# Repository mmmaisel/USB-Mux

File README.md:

# USB-Mux

USB-Mux is an Open-Source and Open-Hardware 2x2 USB 2.0 multiplexer.

It supports a single connection between one of the inputs to one of the outputs.
Additionally, it can disconnect the outputs completely. Power flows from the
selected input to the selected output. Inactive output ports are powerless.

Possible applications are switching USB connections in automated tests
or power-cycle a hanging USB device via software.

Binary production files can be downloaded from the
[Releases](https://github.com/mmmaisel/USB-Mux/releases) page.

## Usage

The multiplexer is controlled over USB via a virtual terminal. The virtual
terminal will prompt "Mux:" and accepts a single number between 0 and 4 followed
by a newline to select the multiplexer position.
The meaning of the different numbers is printed on the PCB.

To connect to the virtual terminal on Linux you can use the following command:
`picocom /dev/ttyACM0`

## Programming

Configure the firmware build environment in the 'src' directory with meson
and the supplied cross compiler file.
`meson . build --cross-file cross.build`
Then go into the 'build' directory and build it with `ninja`.

Now, you can program the CPU on the USB-Mux PCB with OpenOCD and an ST-Nucleo
board as programmer with `ninja flash`.

## License

USB-Mux KiCAD hardware design files in the "hw" directory are licenses under the
CERN-OHL-S v2, or (at your option) any later version.

The USB-Mux firmware in the "src" directory is licensed under the
GNU GPLv3, or (at your option) any later version.

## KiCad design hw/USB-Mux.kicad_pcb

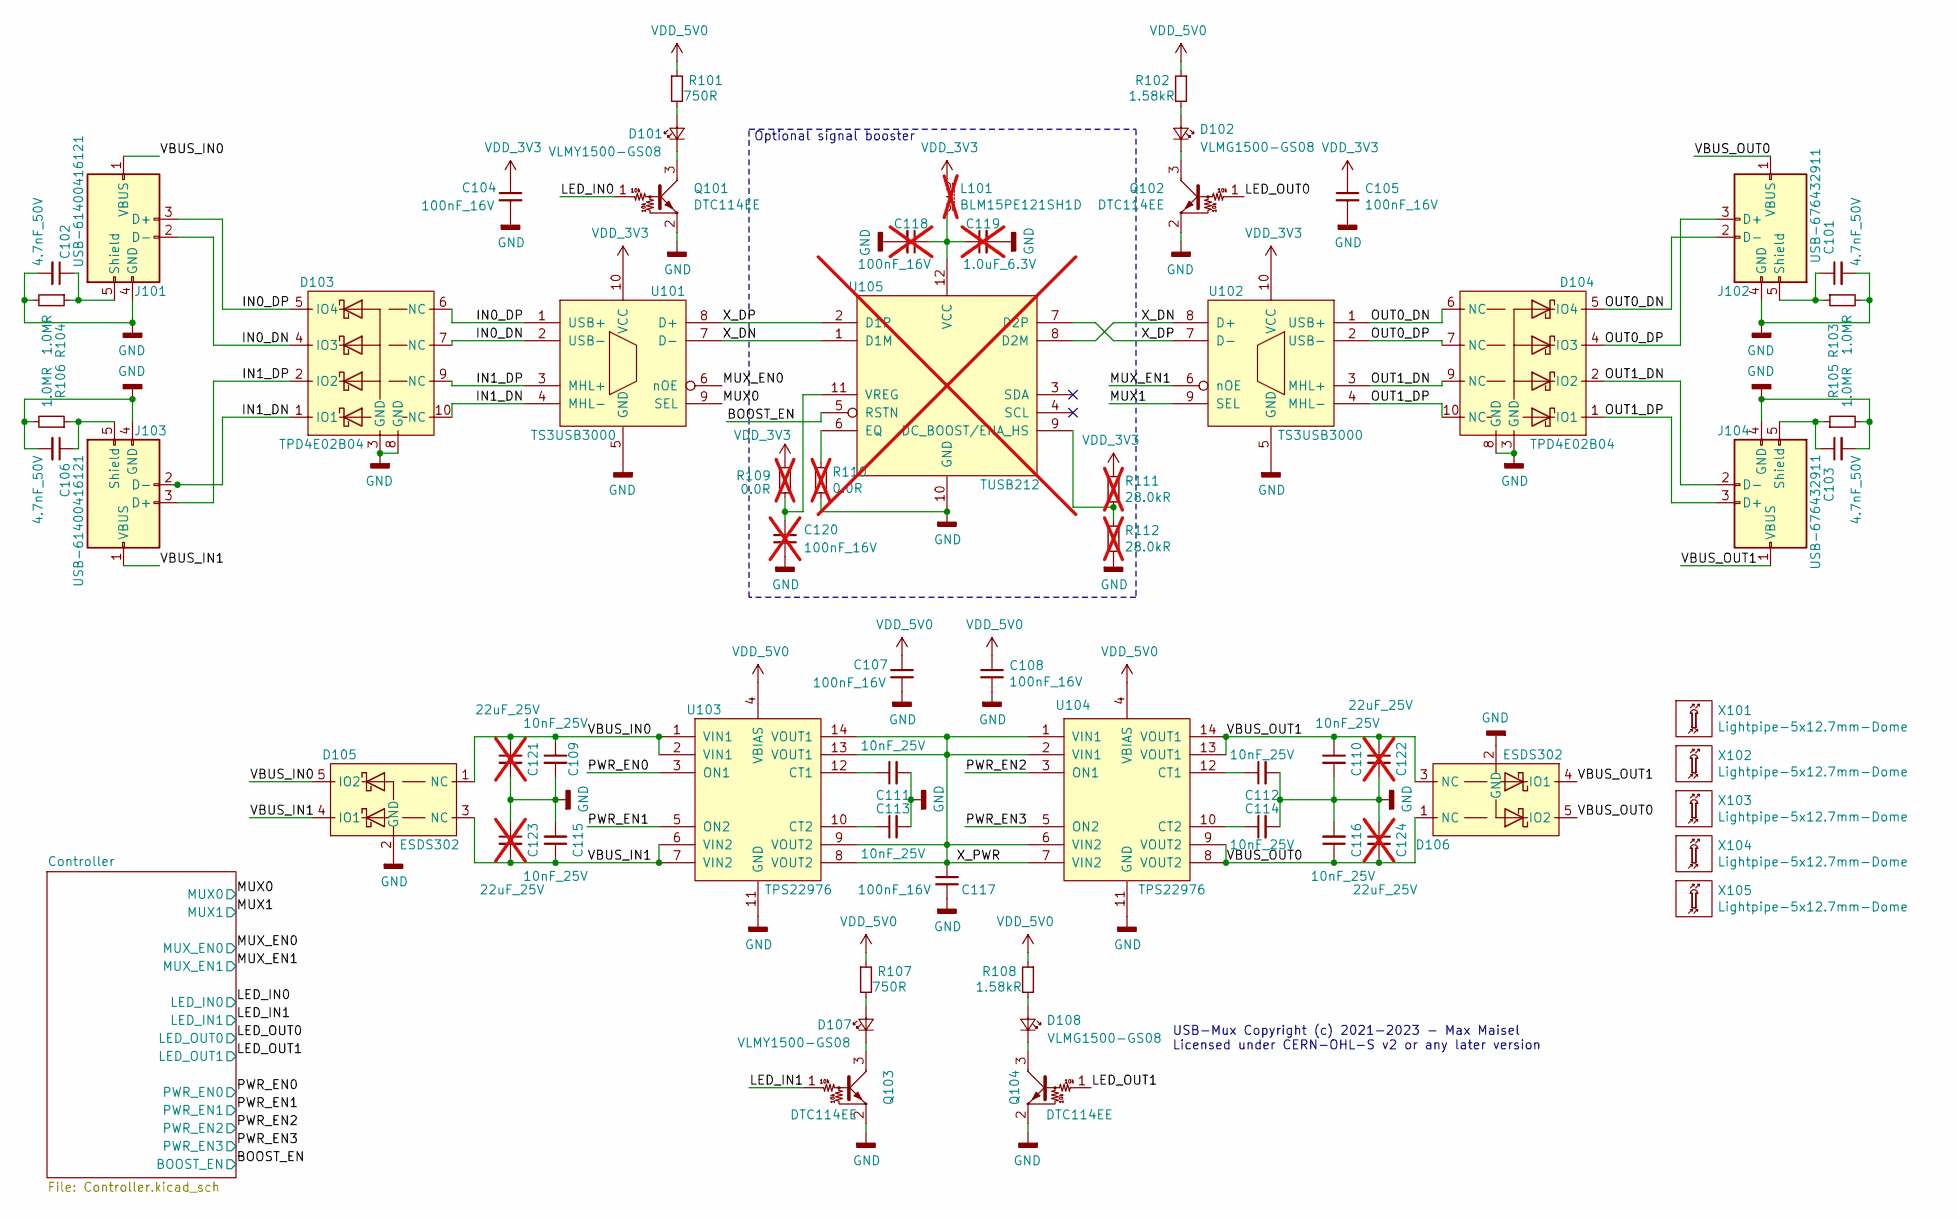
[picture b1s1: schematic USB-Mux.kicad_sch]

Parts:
C101, C102, C103, C106: 4.7nF_50V; C_0402; mouser# 810-CGA2B2X7R1H472K
C104, C105, C107, C108, C117: 100nF_16V; C_0402; mouser# 80-C0402C104K4R
C109, C110, C111, C112, C113, C114, C115, C116: 10nF_25V; C_0402; mouser# 603-CC0402KRX5R8BB10
C118, C120: 100nF_16V; C_0402; mouser# 80-C0402C104K4R; not fitted
C119: 1.0uF_6.3V; C_0402; mouser# 81-GRM152R60J105ME5D; not fitted
C121, C122, C123, C124: 22uF_25V; C_1206; mouser# 81-GRT31CR61E226ME1L; not fitted
D101, D107: VLMY1500-GS08; LED_0402; mouser# 78-VLMY1500-GS08
D102, D108: VLMG1500-GS08; LED_0402; mouser# 78-VLMG1500-GS08
D103, D104: TPD4E02B04; USON10; mouser# 595-TPD4E02B04DQAR
D105, D106: ESDS302; SOT-23-5; mouser# 595-ESDS302DBVR
J101, J103: USB-61400416121
J102, J104: USB-676432911; mouser# 649-87520-0012BLF
L101: BLM15PE121SH1D; L_0402; mouser# 81-BLM15PE121SH1D; not fitted
Q101, Q102, Q103, Q104: DTC114EE; SC-75; mouser# 863-DTC114EET1G
R101, R107: 750R; R_0402; mouser# 667-ERJ-XGNF7500Y
R102, R108: 1.58kR; R_0402; mouser# 667-ERJ-2RKF1581X
R103, R104, R105, R106: 1.0MR; R_0402; mouser# 667-ERJ-2RKF1004X
R109, R110: 0.0R; R_0402; mouser# 667-ERJ-2GE0R00X; not fitted
R111, R112: 28.0kR; R_0402; mouser# 667-ERJ-2RKF2802X; not fitted
U101, U102: TS3USB3000; UQFN10-RSE; mouser# 595-TS3USB3000RSER
U103, U104: TPS22976; WSON-14
U105: TUSB212; X2QFN12-RWB; mouser# 595-TUSB212RWBR; not fitted
X101, X102, X103, X104, X105: Lightpipe-5x12.7mm-Dome; Lightpipe-51513530500F; mouser# 645-51513530500F

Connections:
/BOOST_EN: U105.5 (RSTN); also elsewhere on the board
/IN0_DN: D103.4 (IO3), D103.7 (NC), J101.2 (D-), U101.2 (USB-)
/IN0_DP: D103.5 (IO4), D103.6 (NC), J101.3 (D+), U101.1 (USB+)
/IN1_DN: D103.1 (IO1), D103.10 (NC), J103.2 (D-), U101.4 (MHL-)
/IN1_DP: D103.2 (IO2), D103.9 (NC), J103.3 (D+), U101.3 (MHL+)
/LED_IN0: Q101.1 (B); also elsewhere on the board
/LED_IN1: Q103.1 (B); also elsewhere on the board
/LED_OUT0: Q102.1 (B); also elsewhere on the board
/LED_OUT1: Q104.1 (B); also elsewhere on the board
/MUX0: U101.9 (SEL); also elsewhere on the board
/MUX1: U102.9 (SEL); also elsewhere on the board
/MUX_EN0: U101.6 (nOE); also elsewhere on the board
/MUX_EN1: U102.6 (nOE); also elsewhere on the board
/OUT0_DN: D104.5 (IO4), D104.6 (NC), J102.2 (D-), U102.1 (USB+)
/OUT0_DP: D104.4 (IO3), D104.7 (NC), J102.3 (D+), U102.2 (USB-)
/OUT1_DN: D104.2 (IO2), D104.9 (NC), J104.2 (D-), U102.3 (MHL+)
/OUT1_DP: D104.1 (IO1), D104.10 (NC), J104.3 (D+), U102.4 (MHL-)
/PWR_EN0: U103.3 (ON1); also elsewhere on the board
/PWR_EN1: U103.5 (ON2); also elsewhere on the board
/PWR_EN2: U104.3 (ON1); also elsewhere on the board
/PWR_EN3: U104.5 (ON2); also elsewhere on the board
/VBUS_IN0: C109.1, C121.1, D105.1 (NC), D105.5 (IO2), J101.1 (VBUS), U103.1 (VIN1), U103.2 (VIN1)
/VBUS_IN1: C115.1, C123.2, D105.3 (NC), D105.4 (IO1), J103.1 (VBUS), U103.6 (VIN2), U103.7 (VIN2)
/VBUS_OUT0: C116.1, C124.2, D106.1 (NC), D106.5 (IO2), J102.1 (VBUS), U104.8 (VOUT2), U104.9 (VOUT2)
/VBUS_OUT1: C110.1, C122.1, D106.3 (NC), D106.4 (IO1), J104.1 (VBUS), U104.13 (VOUT1), U104.14 (VOUT1)
/X_DN: U101.7 (D-), U102.8 (D+), U105.1 (D1M), U105.8 (D2M)
/X_DP: U101.8 (D+), U102.7 (D-), U105.2 (D1P), U105.7 (D2P)
/X_PWR: C117.1, U103.8 (VOUT2), U103.9 (VOUT2), U103.13 (VOUT1), U103.14 (VOUT1), U104.1 (VIN1), U104.2 (VIN1), U104.6 (VIN2), U104.7 (VIN2)
GND: C101.2, C102.2, C103.2, C104.2, C105.2, C106.2, C107.2, C108.2, C109.2, C110.2, C111.2, C112.2, C113.2, C114.2, C115.2, C116.2, C117.2, C118.2, C119.2, C120.2, C121.2, C122.2, C123.1, C124.1, D103.3 (GND), D103.8 (GND), D104.3 (GND), D104.8 (GND), D105.2 (GND), D106.2 (GND), J101.4 (GND), J102.4 (GND), J103.4 (GND), J104.4 (GND), Q101.2 (E), Q102.2 (E), Q103.2 (E), Q104.2 (E), R103.2, R104.2, R105.2, R106.2, R110.2, R112.2, U101.5 (GND), U102.5 (GND), U103.11 (GND), U104.11 (GND), U105.10 (GND); also elsewhere on the board
unnamed: C101.1, J102.5 (Shield), R103.1
unnamed: C102.1, J101.5 (Shield), R104.1
unnamed: C103.1, J104.5 (Shield), R105.1
unnamed: C106.1, J103.5 (Shield), R106.1
unnamed: C111.1, U103.12 (CT1)
unnamed: C112.1, U104.12 (CT1)
unnamed: C113.1, U103.10 (CT2)
unnamed: C114.1, U104.10 (CT2)
unnamed: C118.1, C119.1, L101.2, U105.12 (VCC)
unnamed: C120.1, R109.1, U105.11 (VREG)
unnamed: D101.1 (K), Q101.3 (C)
unnamed: D101.2 (A), R101.2
unnamed: D102.1 (K), Q102.3 (C)
unnamed: D102.2 (A), R102.2
unnamed: D107.1 (K), Q103.3 (C)
unnamed: D107.2 (A), R107.2
unnamed: D108.1 (K), Q104.3 (C)
unnamed: D108.2 (A), R108.2
unnamed: R110.1, U105.6 (EQ)
unnamed: R111.2, R112.1, U105.9 (DC_BOOST/ENA_HS)
VDD_3V3: C104.1, C105.1, L101.1, R109.2, R111.1, U101.10 (VCC), U102.10 (VCC); also elsewhere on the board
VDD_5V0: C107.1, C108.1, R101.1, R102.1, R107.1, R108.1, U103.4 (VBIAS), U104.4 (VBIAS); also elsewhere on the board

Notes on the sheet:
Optional signal booster
USB-Mux Copyright (c) 2021-2023 - Max Maisel Licensed under CERN-OHL-S v2 or any later version

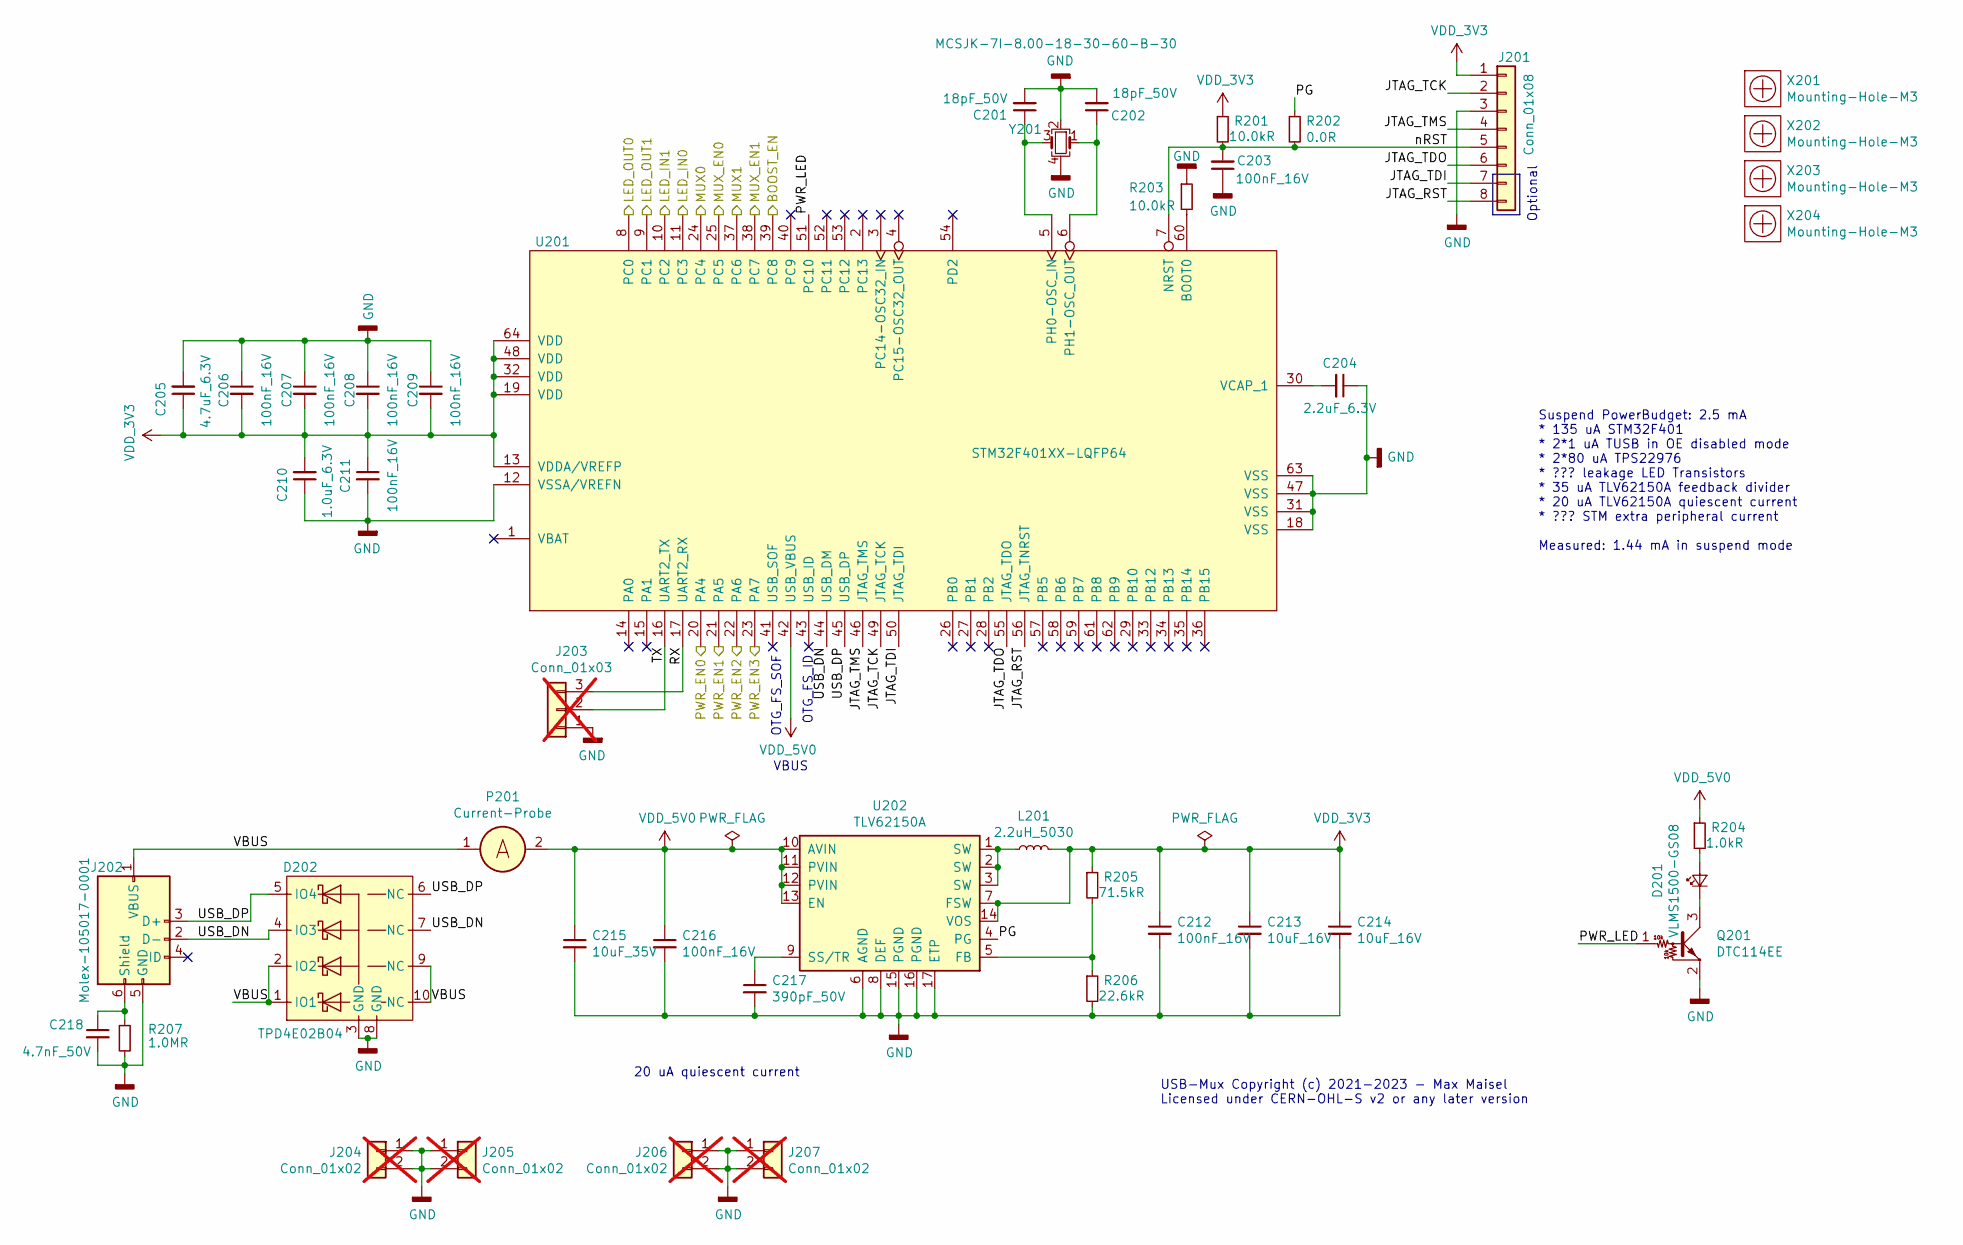
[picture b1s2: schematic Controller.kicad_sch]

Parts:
C201, C202: 18pF_50V; C_0402; mouser# 81-GRM1555C1H180FA1D
C203, C206, C207, C208, C209, C211, C212, C216: 100nF_16V; C_0402; mouser# 80-C0402C104K4R
C204: 2.2uF_6.3V; C_0402; mouser# 81-GRM155R60J225ME9D
C205: 4.7uF_6.3V; C_0402; mouser# 81-GRM155R60J475ME7D
C210: 1.0uF_6.3V; C_0402; mouser# 81-GRM152R60J105ME5D
C213, C214: 10uF_16V; C_1206; mouser# 80-C1206C106K4P
C215: 10uF_35V; C_1210; mouser# 963-GMK325BJ106KN-T
C217: 390pF_50V; C_0402; mouser# 81-GRM155R71H391KA1D
C218: 4.7nF_50V; C_0402; mouser# 810-CGA2B2X7R1H472K
D201: VLMS1500-GS08; LED_0402; mouser# 78-VLMS1500-GS08
D202: TPD4E02B04; USON10; mouser# 595-TPD4E02B04DQAR
J201: Conn_01x08; Pin_Header_Straight_1x08_Pitch2.54mm; farnell# 1593416
J202: Molex-105017-0001; microUSB-B-Molex-1050170-001; mouser# 538-105017-0001
J203: Conn_01x03; Pin_Header_Straight_1x03_Pitch2.54mm; farnell# 1593412; not fitted
J204, J205, J206, J207: Conn_01x02; Pin_Header_Straight_1x02_Pitch2.54mm; farnell# 1593411; not fitted
L201: 2.2uH_5030; L_Taiyo-Yuden_NR-50xx; mouser# 963-NRS5030T2R2NMGJV
P201: Current-Probe; Current-Probe-2.54
Q201: DTC114EE; SC-75; mouser# 863-DTC114EET1G
R201, R203: 10.0kR; R_0402; mouser# 667-ERJ-2RKF1002X
R202: 0.0R; R_0402; mouser# 667-ERJ-2GE0R00X
R204: 1.0kR; R_0402; mouser# 667-ERJ-2RKF1001X
R205: 71.5kR; R_0402; mouser# 667-ERJ-2RKF7152X
R206: 22.6kR; R_0402; mouser# 667-ERJ-S02F2262X
R207: 1.0MR; R_0402; mouser# 667-ERJ-2RKF1004X
U201: STM32F401XX-LQFP64; LQFP-64
U202: TLV62150A; VQFN16-RGT; mouser# 595-TLV62150ARGTR
X201, X202, X203, X204: Mounting-Hole-M3
Y201: MCSJK-7I-8.00-18-30-60-B-30; Crystal_SMD_Multicomp_5032; farnell# 2854013

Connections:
/BOOST_EN: U201.39 (PC8); also elsewhere on the board
/Controller/JTAG_RST: J201.8, U201.56 (JTAG_TNRST)
/Controller/JTAG_TCK: J201.2, U201.49 (JTAG_TCK)
/Controller/JTAG_TDI: J201.7, U201.50 (JTAG_TDI)
/Controller/JTAG_TDO: J201.6, U201.55 (JTAG_TDO)
/Controller/JTAG_TMS: J201.4, U201.46 (JTAG_TMS)
/Controller/PG: R202.1, U202.4 (PG)
/Controller/PWR_LED: Q201.1 (B), U201.51 (PC10)
/Controller/RX: J203.3, U201.17 (UART2_RX)
/Controller/TX: J203.2, U201.16 (UART2_TX)
/Controller/USB_DN: D202.4 (IO3), D202.7 (NC), J202.2 (D-), U201.44 (USB_DM)
/Controller/USB_DP: D202.5 (IO4), D202.6 (NC), J202.3 (D+), U201.45 (USB_DP)
/Controller/VBUS: D202.1 (IO1), D202.2 (IO2), D202.9 (NC), D202.10 (NC), J202.1 (VBUS), P201.1
/Controller/nRST: C203.2, J201.5, R201.2, R202.2, U201.7 (NRST)
/LED_IN0: U201.11 (PC3); also elsewhere on the board
/LED_IN1: U201.10 (PC2); also elsewhere on the board
/LED_OUT0: U201.8 (PC0); also elsewhere on the board
/LED_OUT1: U201.9 (PC1); also elsewhere on the board
/MUX0: U201.24 (PC4); also elsewhere on the board
/MUX1: U201.37 (PC6); also elsewhere on the board
/MUX_EN0: U201.25 (PC5); also elsewhere on the board
/MUX_EN1: U201.38 (PC7); also elsewhere on the board
/PWR_EN0: U201.20 (PA4); also elsewhere on the board
/PWR_EN1: U201.21 (PA5); also elsewhere on the board
/PWR_EN2: U201.22 (PA6); also elsewhere on the board
/PWR_EN3: U201.23 (PA7); also elsewhere on the board
GND: C201.2, C202.2, C203.1, C204.1, C205.2, C206.1, C207.1, C208.1, C209.1, C210.1, C211.2, C212.2, C213.2, C214.2, C215.2, C216.2, C217.2, C218.2, D202.3 (GND), D202.8 (GND), J201.3, J202.5 (GND), J203.1, J204.1, J204.2, J205.1, J205.2, J206.1, J206.2, J207.1, J207.2, Q201.2 (E), R203.1, R206.2, R207.2, U201.12 (VSSA/VREFN), U201.18 (VSS), U201.31 (VSS), U201.47 (VSS), U201.63 (VSS), U202.6 (AGND), U202.8 (DEF), U202.15 (PGND), U202.16 (PGND), U202.17 (ETP), Y201.2, Y201.4; also elsewhere on the board
unnamed: C201.1, U201.5 (PH0-OSC_IN), Y201.3
unnamed: C202.1, U201.6 (PH1-OSC_OUT), Y201.1
unnamed: C204.2, U201.30 (VCAP_1)
unnamed: C217.1, U202.9 (SS/TR)
unnamed: C218.1, J202.6 (Shield), R207.1
unnamed: D201.1 (K), Q201.3 (C)
unnamed: D201.2 (A), R204.2
unnamed: L201.1, U202.1 (SW), U202.2 (SW), U202.3 (SW)
unnamed: R203.2, U201.60 (BOOT0)
unnamed: R205.2, R206.1, U202.5 (FB)
VDD_3V3: C205.1, C206.2, C207.2, C208.2, C209.2, C210.2, C211.1, C212.1, C213.1, C214.1, J201.1, L201.2, R201.1, R205.1, U201.13 (VDDA/VREFP), U201.19 (VDD), U201.32 (VDD), U201.48 (VDD), U201.64 (VDD), U202.7 (FSW), U202.14 (VOS); also elsewhere on the board
VDD_5V0: C215.1, C216.1, P201.2, R204.1, U201.42 (USB_VBUS), U202.10 (AVIN), U202.11 (PVIN), U202.12 (PVIN), U202.13 (EN); also elsewhere on the board

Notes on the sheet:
USB-Mux Copyright (c) 2021-2023 - Max Maisel Licensed under CERN-OHL-S v2 or any later version
VBUS
OTG_FS_SOF
Optional
20 uA quiescent current
OTG_FS_ID
Suspend PowerBudget: 2.5 mA * 135 uA STM32F401 * 2*1 uA TUSB in OE disabled mode * 2*80 uA TPS22976 * ??? leakage LED Transistors * 35 uA TLV62150A feedback divider * 20 uA TLV62150A quiescent current * ??? STM extra peripheral current Measured: 1.44 mA in suspend mode

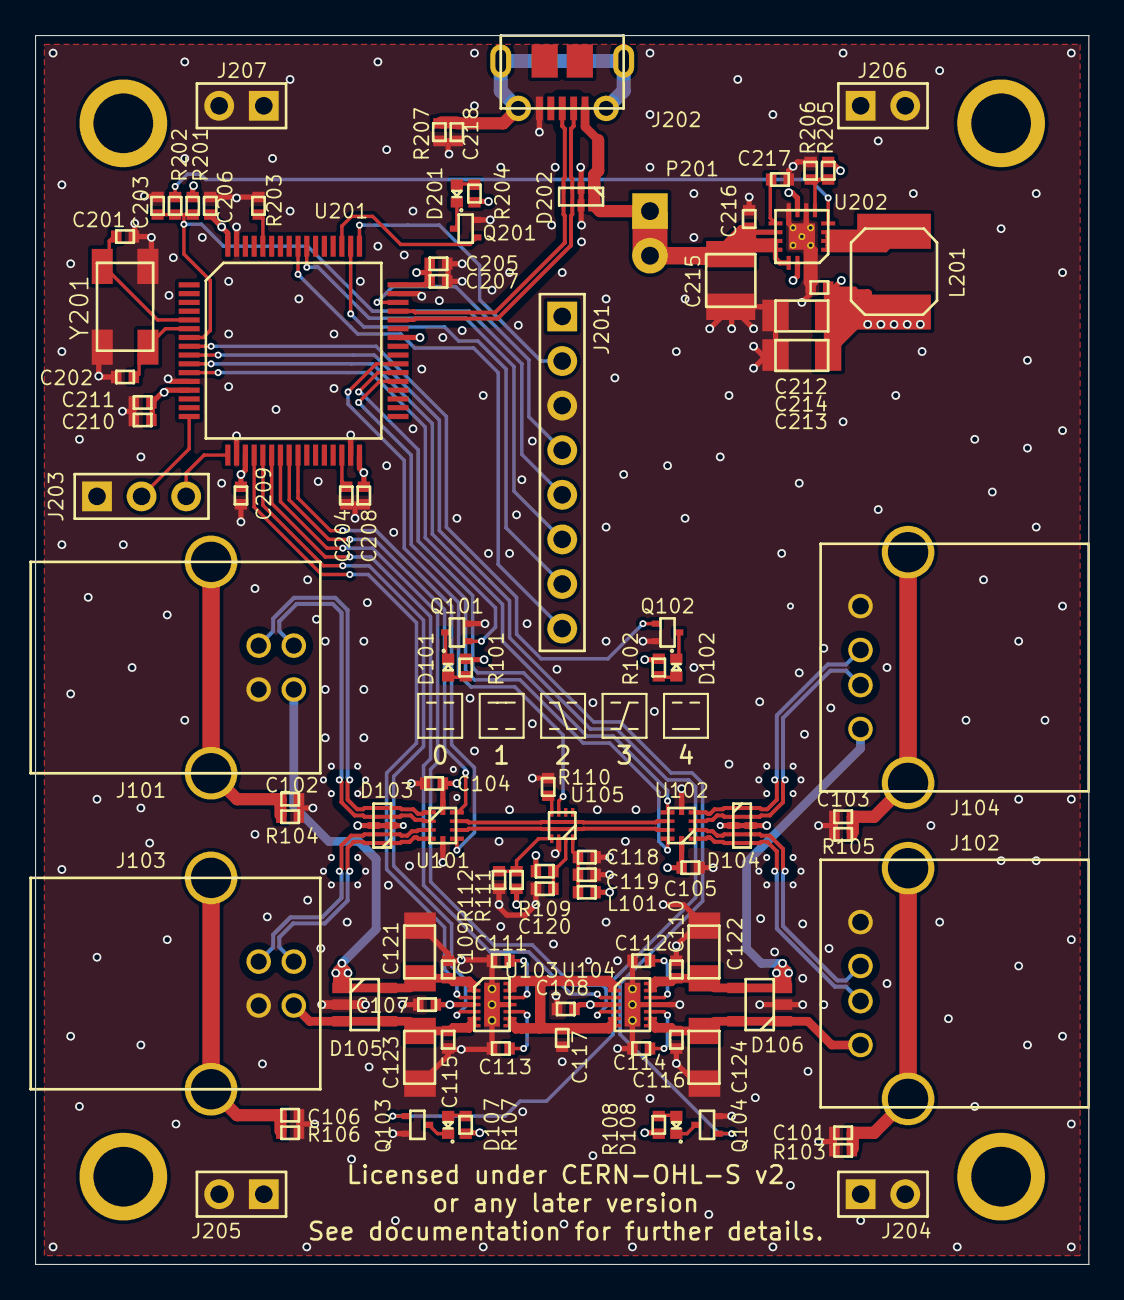
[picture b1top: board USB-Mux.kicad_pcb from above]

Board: 6 copper layers, 60.0 x 70.0 mm, 107 parts (0 on the bottom side), 74 nets.

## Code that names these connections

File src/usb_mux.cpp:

/**********************************************************************\
 * USB-Mux
 *
 * USB-Mux class
 **********************************************************************
 * Copyright (C) 2021 - Max Maisel
 *
 * This program is free software; you can redistribute it and/or
 * modify it under the terms of the GNU General Public License
 * as published by the Free Software Foundation; either version 2
 * of the License, or (at your option) any later version.
 *
 * This program is distributed in the hope that it will be useful,
 * but WITHOUT ANY WARRANTY; without even the implied warranty of
 * MERCHANTABILITY or FITNESS FOR A PARTICULAR PURPOSE.  See the
 * GNU General Public License for more details.
 *
 * You should have received a copy of the GNU General Public License
 * along with this program.  If not, see <http://www.gnu.org/licenses/>.
\**********************************************************************/
#include "usb_mux.h"
#include "pinout.h"
#include "system.h"

#include "dev/gpio.h"
#include "dev/rcc.h"

using namespace dev;
using namespace dev::rcc;
using namespace pinout;

void UsbMux::initialize() {
    RCC->AHB1ENR |= GPIOAEN | GPIOCEN;

    GPIOA->MODER |= MODE_PWREN0 | MODE_PWREN1 | MODE_PWREN2 | MODE_PWREN3;
    GPIOC->PUPDR |= PUPD_MUXDIS0 | PUPD_MUXDIS1 | PUPD_BOOSTDIS;
    GPIOC->MODER |= MODE_LED_OUT0 | MODE_LED_OUT1 |
        MODE_LED_IN0 | MODE_LED_IN1 | MODE_LED_PWR |
        MODE_MUX0 | MODE_MUX1 | MODE_MUXDIS0 | MODE_MUXDIS1 |
        MODE_BOOSTDIS;

    disable_mux();
    GPIOC->set_odr(LED_PWR);
}

void UsbMux::mux(BYTE pos) {
    disable_mux();
    switch(pos) {
        case 1:
            GPIOA->set_odr(PWREN0 | PWREN2);
            sleep_ms(1);
            GPIOC->set_odr(MUX1);
            sleep_ms(1);
            GPIOC->clear_odr(MUXDIS0 | MUXDIS1);
            GPIOC->set_odr(LED_IN0 | LED_OUT0);
            break;
        case 2:
            GPIOA->set_odr(PWREN0 | PWREN3);
            sleep_ms(2);
            GPIOC->clear_odr(MUXDIS0 | MUXDIS1);
            GPIOC->set_odr(LED_IN0 | LED_OUT1);
            break;
        case 3:
            GPIOA->set_odr(PWREN1 | PWREN2);
            sleep_ms(1);
            GPIOC->set_odr(MUX0 | MUX1);
            sleep_ms(1);
            GPIOC->clear_odr(MUXDIS0 | MUXDIS1);
            GPIOC->set_odr(LED_IN1 | LED_OUT0);
            break;
        case 4:
            GPIOA->set_odr(PWREN1 | PWREN3);
            sleep_ms(1);
            GPIOC->set_odr(MUX0);
            sleep_ms(1);
            GPIOC->clear_odr(MUXDIS0 | MUXDIS1);
            GPIOC->set_odr(LED_IN1 | LED_OUT1);
            break;
        default:
            break;
    };
}

void UsbMux::disable_mux() {
    GPIOC->set_odr(MUXDIS0 | MUXDIS1);
    sleep_ms(1);
    GPIOA->clear_odr(
        PWREN0 | PWREN1 | PWREN2 | PWREN3
    );
    GPIOC->clear_odr(
        LED_OUT0 | LED_OUT1 | LED_IN0 | LED_IN1 | MUX0 | MUX1
    );
}

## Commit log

2021-08-02 Add license and readme.
2021-12-30 Commit USB-Mux KiCAD library.
2021-12-30 Add USB-Mux hardware design.
2021-12-30 Fix swapped pin label in USB-Mux schematic.
2021-12-30 Add minimal firmware.
2021-12-30 Implement USB-Muxer class.
2021-12-30 Add TS3USB3000RSER component, footprint and 3D model.
2021-12-30 Add ESDS302 component, footprint and 3D model.
2021-12-30 OpenOCD: Connect under reset.
2021-12-30 Fix and cleanup USB control endpoint implementation
2021-12-30 Add SMA-73251-1150 component, footprint and 3D model.
2021-12-30 Add rendered image to readme.
2021-12-30 Add two more passive components.
2021-12-30 Implement bulk endpoints and CDC.
2021-12-30 Enter stop mode on USB suspend.
2021-12-30 Implement USB physical device driver.
    Needs endpoint driver to compile.
2021-12-30 Implement multi packet USB TX and use CDC descriptor.
2021-12-30 Add TPD4E02B04 component, footprint and 3D model.
2021-12-30 First Mux terminal and parser implementation.
2021-12-30 Add TUSB212 and TUSB216 component, footprint and 3D model.
2021-12-30 Implement nice Mux TTY.
2021-12-30 Implement USB endpoint device driver.
2021-12-30 Implement USB Descriptors, currently for a keyboard.
2021-12-30 Add two more basic connector components, footprints and 3D models.
2021-12-30 Split USB endpoint into multiple files, create dummy classes for CDC.
2021-12-30 Add 100R resistor component.
2022-01-10 Add BLM15PE121SH1D component, footprint and 3D model.
2022-01-12 Update USB-Mux schematic.
    Use new USB-Mux chip, add redriver and ESD protection.
2022-01-15 Layout USB-Mux rev2.
2022-01-27 Update project to KiCad 6 file formats.
2022-02-24 Cleanup Library
    Remove unused ESD diode component and consistently name resistors X.XR.
2022-02-24 Use alternate functions for STM32 pins.
2023-01-30 Improve Layout, use impedances from manufacturer.
2023-01-30 USB code improvements.
2023-03-26 Adjust software to rev 2 pinout.
2023-03-26 Update rendering to rev 2.
2023-03-29 Add case for the USB-Mux device.
2023-03-29 Port build system to meson and release revision 2.
2023-04-01 Upgrade project to KiCAD 7.0.
2023-04-01 Mark dnp components in schematic.
2023-04-15 Update readme.
2023-04-15 Add download link to readme.
2023-04-22 Use VID/PID from pid.codes.
2023-04-22 Add some missing component ordering numbers.
2023-04-22 Increase Case-Top text and lightpipe hole size.
